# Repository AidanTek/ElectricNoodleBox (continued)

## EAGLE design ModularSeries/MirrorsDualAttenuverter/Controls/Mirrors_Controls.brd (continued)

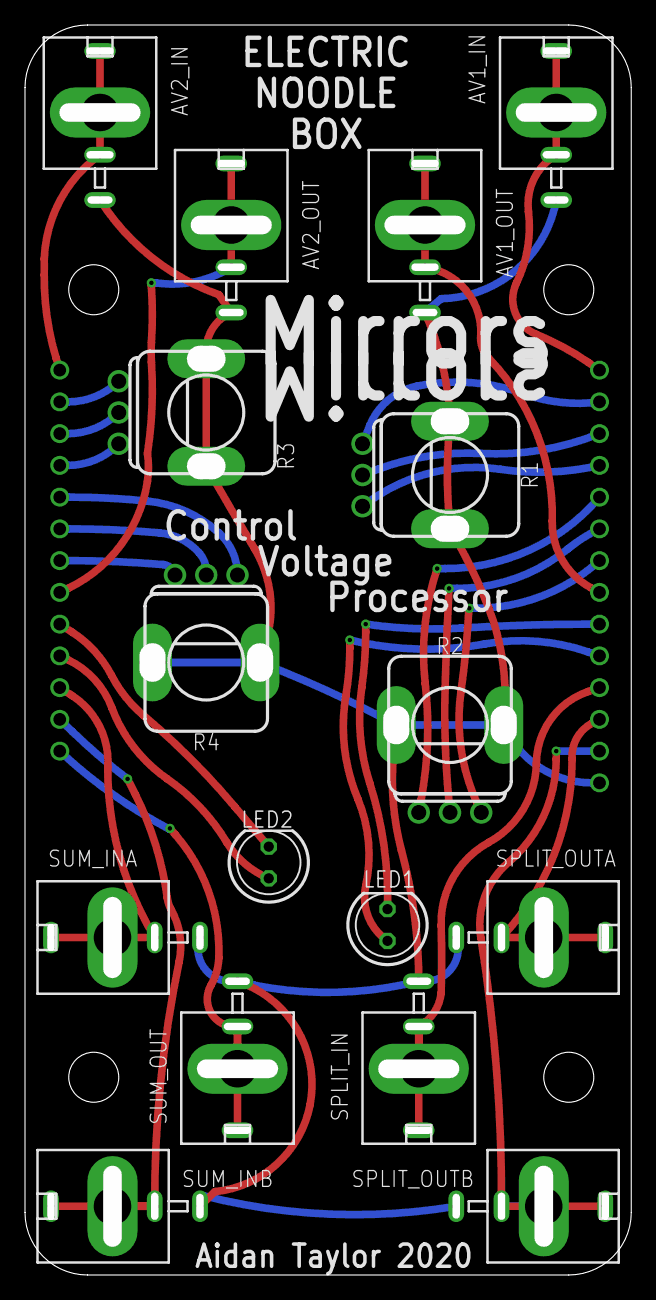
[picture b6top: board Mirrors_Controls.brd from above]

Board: 2 copper layers, 48.5 x 100.0 mm, 17 parts (1 on the bottom side), 27 nets.
